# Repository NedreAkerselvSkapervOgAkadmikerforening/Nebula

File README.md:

# Nebula
## Introduksjon
Nebula er foreningen NASAs neste generasjons flydatamaskin til bruk i foreningens modellrakketter.

## 🎯 Mål
1. Nebula skal være rask, kompakt, pålitelig, effektiv og enkel i bruk.
2. Nebula skal være bygd modulært, så nye sensorer og systemer kan innbyttes.
3. Sensorene i Nebula skal være nøyaktige og pålitelige.

## 💽 Oppbygning
Nebula kan overordnet deles i to kategorier:
1. Hovedkort
2. Modulene

### 🏠 Hovedkortet
Hovedkortet er hjernen og master i hele flydatamaskinen. Kortet bruker primært SPI-protokoll til å kommunisere med modulene.

Systemet drives av et enkelt 3.7 V LiPo-batteri, med 3.3 V logikk for alle moduler.

**Sensorer:**
- BMP390 - Trykk- og temperatursensor ([lenke](https://www.3achips.com/p/11139403?utm_source=octopart&utm_medium=cpc&utm_campaign=3achips_launch))
- BNO086 - Akselerometer, gyroskop og magnetometer

**Datalogging:**
- MEM2067-02-180-00-A - Hengslet SD kort modul ([lenke](https://no.mouser.com/ProductDetail/GCT/MEM2067-02-180-00-A?qs=KUoIvG%2F9IlYTw%2Fcc1GlNJA%3D%3D&srsltid=AfmBOooPYGt0VKhHioGUMaVG0J4CpHVvJOKDjSTnPHolRedy0QrVqX5W))

**Telemetri:**
- SX1276 - LoRa transceiver for trådløs kommunikasjon med bakken

**Kommunikasjon:**
- USB-C (alternativt micro USB) – for kommunikasjon med PC og programmering

**Strømforsyning:**
- Voltage divider - For å måle spenningen på batteriet gjennom ADC på mikrokontrolleren
- TPS63020 - 3.3V spenningsregulator (VURDER)
- JST 2-pin - For å koble til batteriet
- Power switch - For å slå av og på hele systemet

**Debugging:**
- Power LED - For å indikere at systemet er på
- Status LED - For å indikere systemstatus (f.eks. feil, normal drift, etc.)

### 📨 SPI
Hovedkortet fungerer som master, modulene som slaves. Hver modul har egen CS‑pin, som kan velges ved å lodde over riktig solder pad (CS1–CS6).

Mikrokontrolleren har totalt fire SPI-busser. 2 reserveres til selve hovedkortet, og 2 til modulene.

### 🖇️ Konnektorer
I alle moduler skal det være en 20 pin konnektor som kobler modulen til hovedkortet. Denne skal ha følgende pinout:
- CS: 6 stk
- MISO: 2 stk
- MOSI: 2 stk
- SCK: 2 stk
- 3vO: 1 stk
- GND: 1 stk
- GPIO: 6 stk

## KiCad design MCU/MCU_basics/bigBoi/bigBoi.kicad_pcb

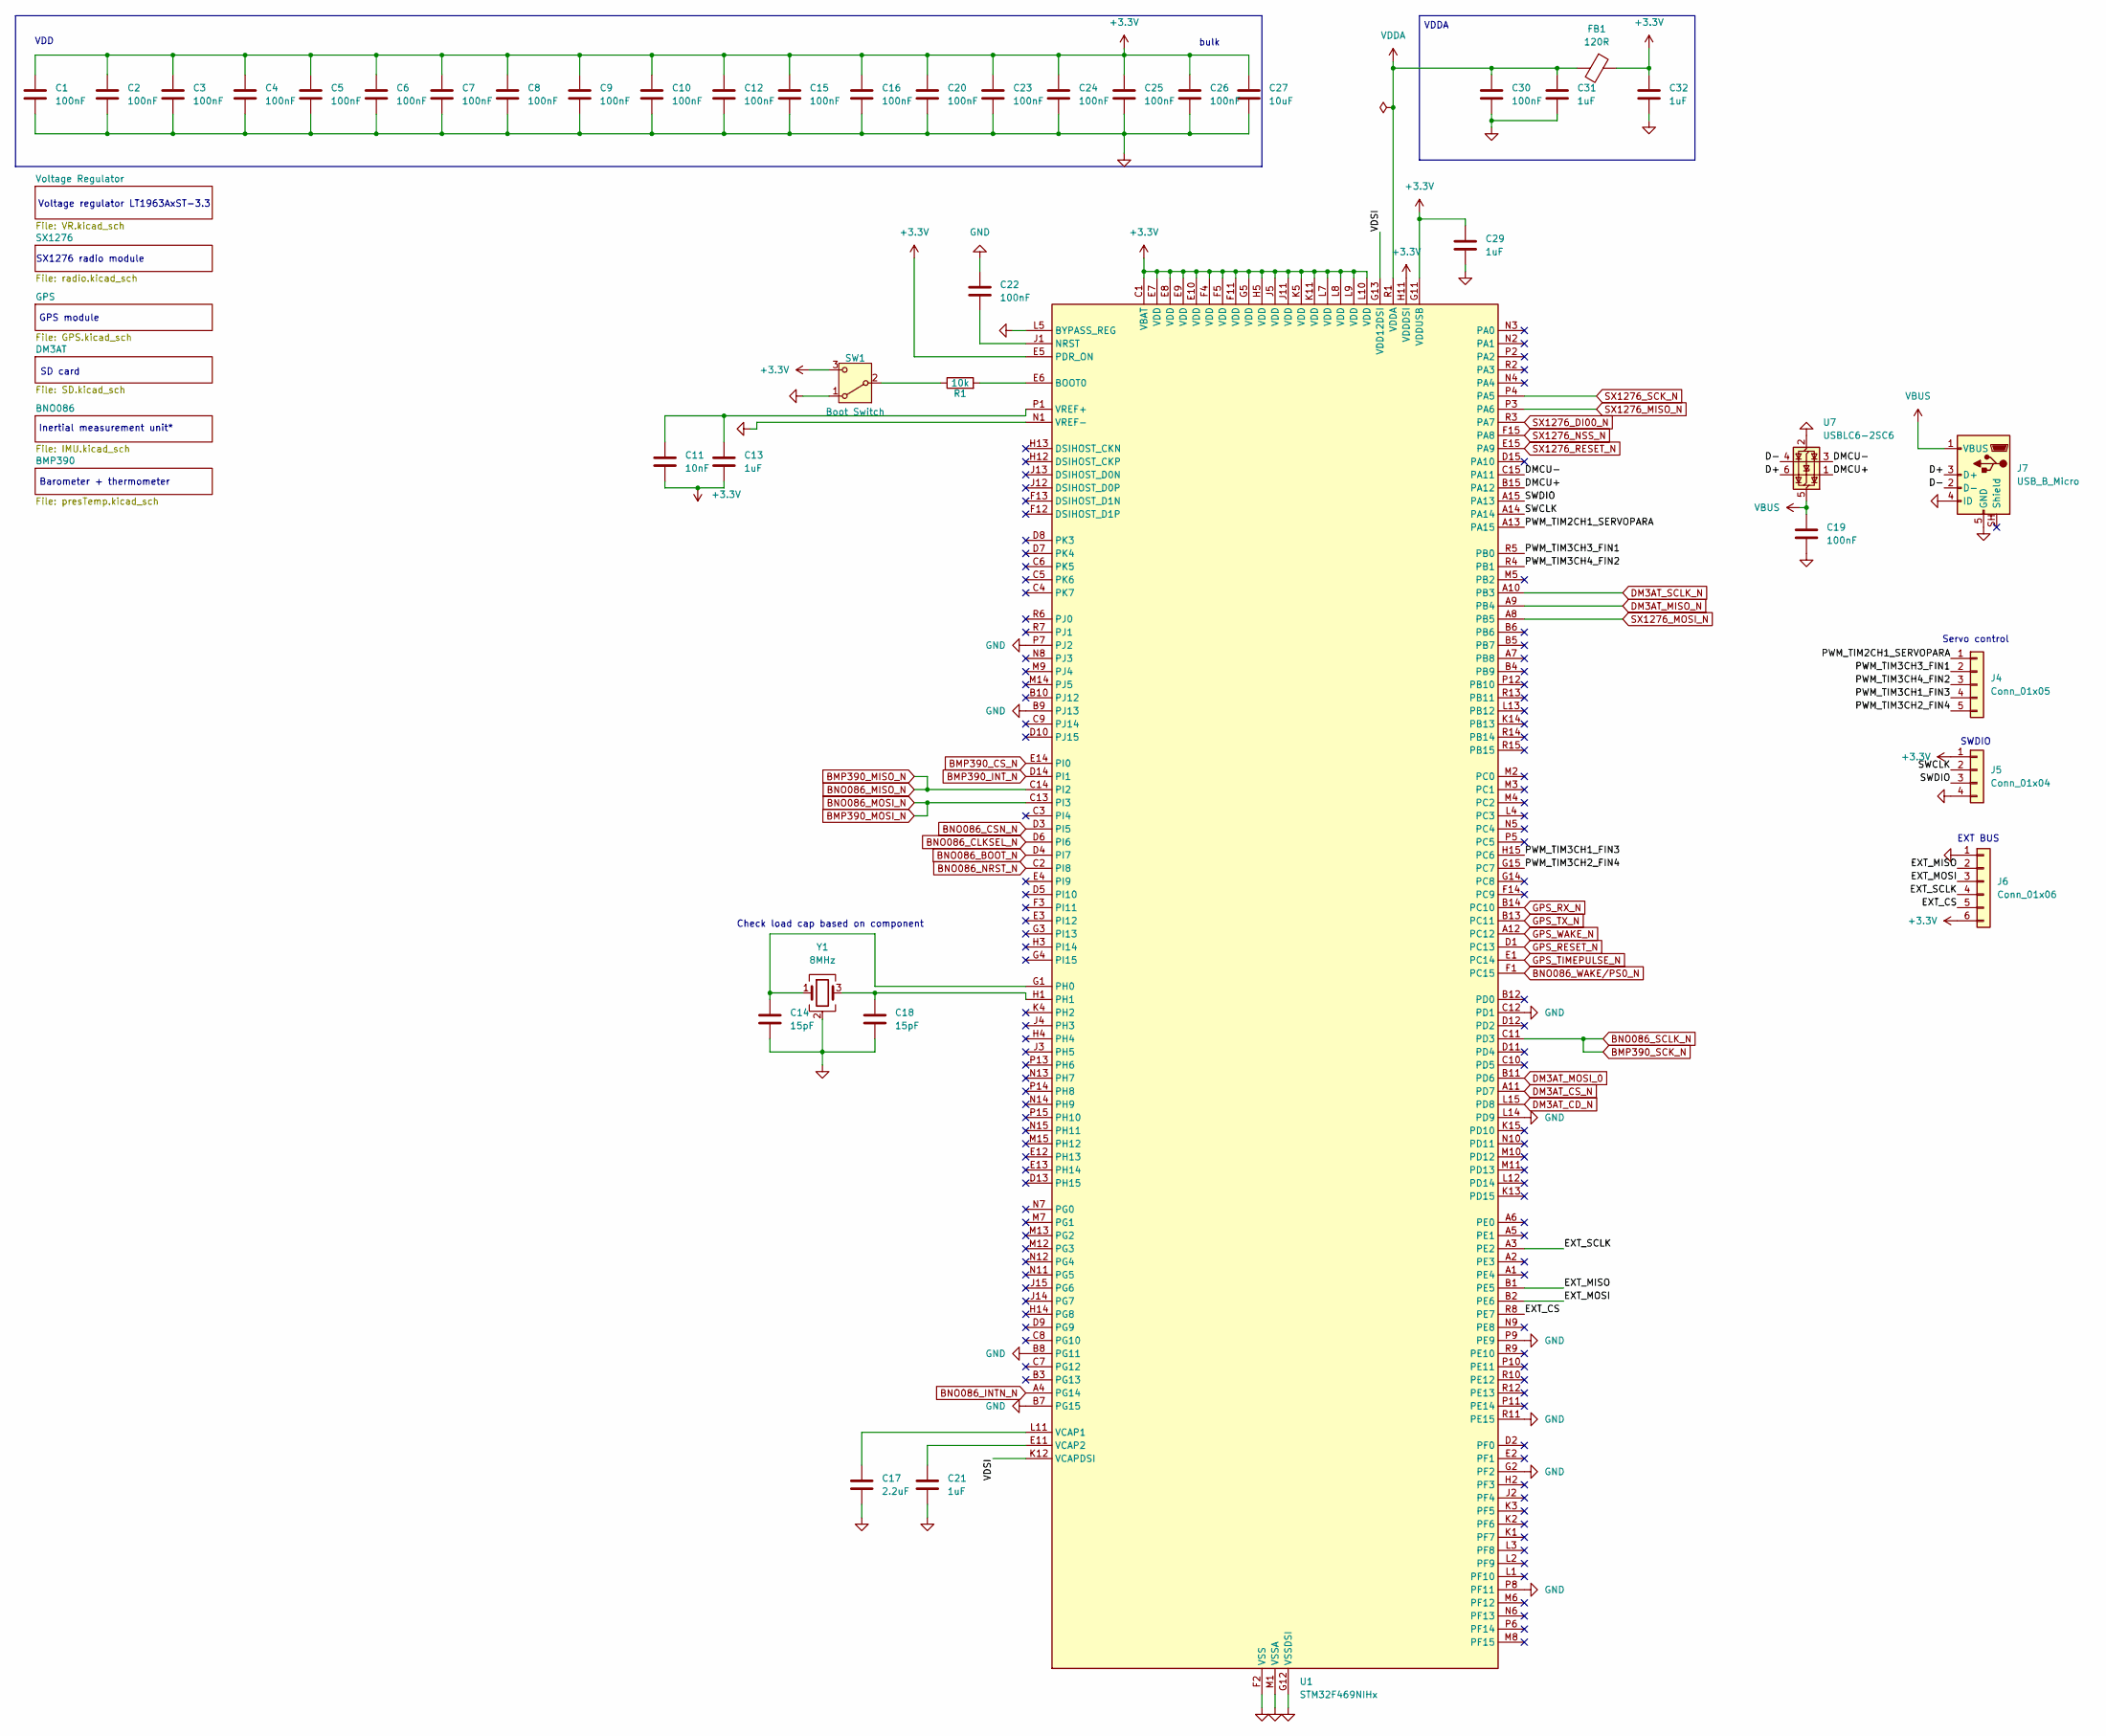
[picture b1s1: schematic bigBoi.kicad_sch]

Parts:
C1, C2, C3, C4, C5, C6, C7, C8, C9, C10, C12, C15, C16, C19, C20, C22, C23, C24, C25, C26, C30: 100nF; C_0402_1005Metric
C11: 10nF; C_0402_1005Metric
C13, C21, C29, C31, C32: 1uF; C_0402_1005Metric
C14, C18: 15pF; C_0402_1005Metric
C17: 2.2uF; C_0603_1608Metric
C27: 10uF; C_0805_2012Metric
FB1: 120R; L_0603_1608Metric
J4: Conn_01x05; PinHeader_1x05_P2.54mm_Vertical
J5: Conn_01x04; PinHeader_1x04_P2.54mm_Vertical
J6: Conn_01x06; PinHeader_1x06_P2.54mm_Vertical
J7: USB_B_Micro; USB_Micro-B_Molex_47346-0001
R1: 10k; R_0402_1005Metric
SW1: Boot Switch; SW_SPDT_PCM12
U1: STM32F469NIHx; TFBGA-216_13x13mm_Layout15x15_P0.8mm
U7: USBLC6-2SC6; SOT-23-6
Y1: 8MHz; Crystal_SMD_3225-4Pin_3.2x2.5mm

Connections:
+3.3V: C1.1, C2.1, C3.1, C4.1, C5.1, C6.1, C7.1, C8.1, C9.1, C10.1, C11.2, C12.1, C13.2, C15.1, C16.1, C20.1, C23.1, C24.1, C25.1, C26.1, C27.1, C29.1, C32.2, FB1.1, J5.1, J6.6, SW1.3 (C), U1.C1 (VBAT), U1.E5 (PDR_ON), U1.E7 (VDD), U1.E8 (VDD), U1.E9 (VDD), U1.E10 (VDD), U1.F4 (VDD), U1.F5 (VDD), U1.F11 (VDD), U1.G5 (VDD), U1.G11 (VDDUSB), U1.H5 (VDD), U1.H11 (VDDDSI), U1.J5 (VDD), U1.J11 (VDD), U1.K5 (VDD), U1.K11 (VDD), U1.L7 (VDD), U1.L8 (VDD), U1.L9 (VDD), U1.L10 (VDD); also elsewhere on the board
/D+: J7.3 (D+), U7.6 (I/O1)
/D-: J7.2 (D-), U7.4 (I/O2)
/DMCU+: U1.B15 (PA12), U7.1 (I/O1)
/DMCU-: U1.C15 (PA11), U7.3 (I/O2)
/EXT_CS: J6.5, U1.R8 (PE7)
/EXT_MISO: J6.2, U1.B1 (PE5)
/EXT_MOSI: J6.3, U1.B2 (PE6)
/EXT_SCLK: J6.4, U1.A3 (PE2)
/PWM_TIM2CH1_SERVOPARA: J4.1, U1.A13 (PA15)
/PWM_TIM3CH1_FIN3: J4.4, U1.H15 (PC6)
/PWM_TIM3CH2_FIN4: J4.5, U1.G15 (PC7)
/PWM_TIM3CH3_FIN1: J4.2, U1.R5 (PB0)
/PWM_TIM3CH4_FIN2: J4.3, U1.R4 (PB1)
/SWCLK: J5.2, U1.A14
/SWDIO: J5.3, U1.A15 (PA13)
/VDSI: U1.G13 (VDD12DSI), U1.K12 (VCAPDSI)
BMP390_CS_N: U1.E14 (PI0); also elsewhere on the board
BMP390_INT_N: U1.D14 (PI1); also elsewhere on the board
BMP390_MISO_N: U1.C14 (PI2); also elsewhere on the board
BMP390_MOSI_N: U1.C13 (PI3); also elsewhere on the board
BMP390_SCK_N: U1.C11 (PD3); also elsewhere on the board
BNO086_BOOT_N: U1.D4 (PI7); also elsewhere on the board
BNO086_CLKSEL_N: U1.D6 (PI6); also elsewhere on the board
BNO086_CSN_N: U1.D3 (PI5); also elsewhere on the board
BNO086_INTN_N: U1.A4 (PG14); also elsewhere on the board
BNO086_NRST_N: U1.C2 (PI8); also elsewhere on the board
BNO086_WAKE/PS0_N: U1.F1 (PC15); also elsewhere on the board
DM3AT_CD_N: U1.L15 (PD8); also elsewhere on the board
DM3AT_CS_N: U1.A11 (PD7); also elsewhere on the board
DM3AT_MISO_N: U1.A9 (PB4); also elsewhere on the board
DM3AT_MOSI_0: U1.B11 (PD6); also elsewhere on the board
DM3AT_SCLK_N: U1.A10 (PB3); also elsewhere on the board
GND: C1.2, C2.2, C3.2, C4.2, C5.2, C6.2, C7.2, C8.2, C9.2, C10.2, C12.2, C14.2, C15.2, C16.2, C17.2, C18.2, C19.2, C20.2, C21.1, C22.1, C23.2, C24.2, C25.2, C26.2, C27.2, C29.2, C30.1, C31.1, C32.1, J5.4, J6.1, J7.4 (ID), J7.5 (GND), SW1.1 (A), U1.B7 (PG15), U1.B8 (PG11), U1.B9 (PJ13), U1.C12 (PD1), U1.F2 (VSS), U1.F6 (VSS), U1.F7 (VSS), U1.F8 (VSS), U1.F9 (VSS), U1.F10 (VSS), U1.G2 (PF2), U1.G6 (VSS), U1.G10 (VSS), U1.G12 (VSSDSI), U1.H6 (VSS), U1.H10 (VSS), U1.J6 (VSS), U1.J10 (VSS), U1.K6 (VSS), U1.K7 (VSS), U1.K8 (VSS), U1.K9 (VSS), U1.K10 (VSS), U1.L5 (BYPASS_REG), U1.L6 (VSS), U1.L14 (PD9), U1.M1 (VSSA), U1.N1 (VREF-), U1.P7 (PJ2), U1.P8 (PF11), U1.P9 (PE9), U1.R11 (PE15), U7.2 (GND), Y1.2 (G), Y1.4 (G); also elsewhere on the board
GPS_RESET_N: U1.D1 (PC13); also elsewhere on the board
GPS_RX_N: U1.B14 (PC10); also elsewhere on the board
GPS_TIMEPULSE_N: U1.E1 (PC14); also elsewhere on the board
GPS_TX_N: U1.B13 (PC11); also elsewhere on the board
GPS_WAKE_N: U1.A12 (PC12); also elsewhere on the board
unnamed: R1.1, SW1.2 (B)
unnamed: R1.2, U1.E6 (BOOT0)
unnamed: C22.2, U1.J1 (NRST)
unnamed: C14.1, U1.G1 (PH0), Y1.1
unnamed: C18.1, U1.H1, Y1.3
unnamed: C17.1, U1.L11 (VCAP1)
unnamed: C21.2, U1.E11 (VCAP2)
unnamed: C11.1, C13.1, U1.P1 (VREF+)
SX1276_DI00_N: U1.R3 (PA7); also elsewhere on the board
SX1276_MISO_N: U1.P3 (PA6); also elsewhere on the board
SX1276_MOSI_N: U1.A8 (PB5); also elsewhere on the board
SX1276_NSS_N: U1.F15 (PA8); also elsewhere on the board
SX1276_RESET_N: U1.E15 (PA9); also elsewhere on the board
SX1276_SCK_N: U1.P4 (PA5); also elsewhere on the board
VBUS: C19.1, J7.1 (VBUS), U7.5 (VBUS); also elsewhere on the board
VDDA: C30.2, C31.2, FB1.2, U1.R1 (VDDA)

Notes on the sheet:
Inertial measurement unit*
bulk
VDD
EXT BUS
GPS module
SD card
VDDA
Voltage regulator LT1963AxST-3.3
Check load cap based on component
SX1276 radio module
Barometer + thermometer
SWDIO
Servo control

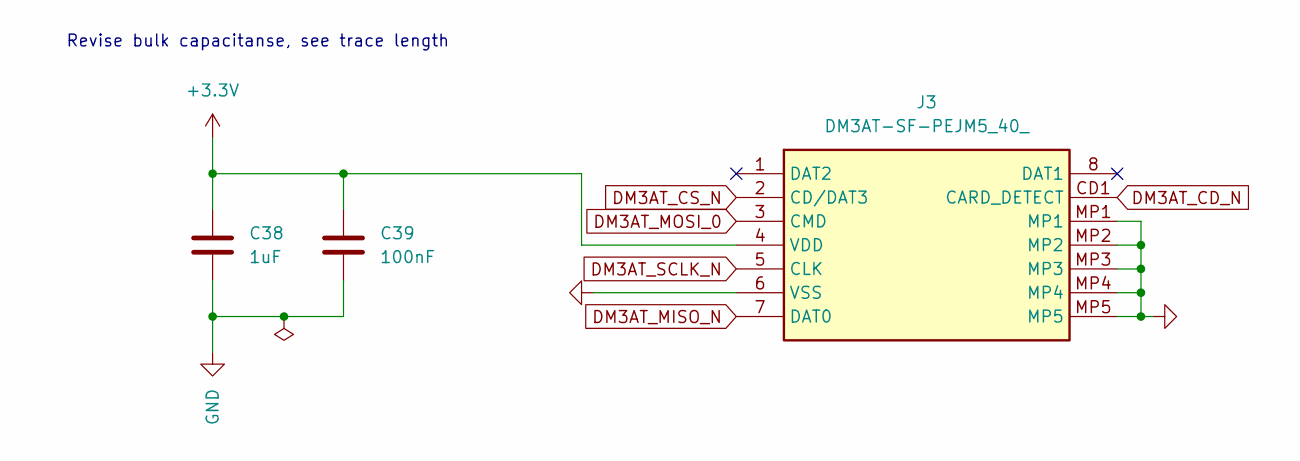
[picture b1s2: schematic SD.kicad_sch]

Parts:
C38: 1uF; C_0402_1005Metric
C39: 100nF; C_0402_1005Metric
J3: DM3AT-SF-PEJM5_40_; DM3ATSFPEJM540; Mouser Part Number 798-DM3AT-SF-PEJM540

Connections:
+3.3V: C38.1, C39.1, J3.4 (VDD); also elsewhere on the board
DM3AT_CD_N: J3.CD1 (CARD_DETECT); also elsewhere on the board
DM3AT_CS_N: J3.2 (CD/DAT3); also elsewhere on the board
DM3AT_MISO_N: J3.7 (DAT0); also elsewhere on the board
DM3AT_MOSI_0: J3.3 (CMD); also elsewhere on the board
DM3AT_SCLK_N: J3.5 (CLK); also elsewhere on the board
GND: C38.2, C39.2, J3.6 (VSS), J3.MP1, J3.MP2, J3.MP3, J3.MP4, J3.MP5; also elsewhere on the board

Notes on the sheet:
Revise bulk capacitanse, see trace length

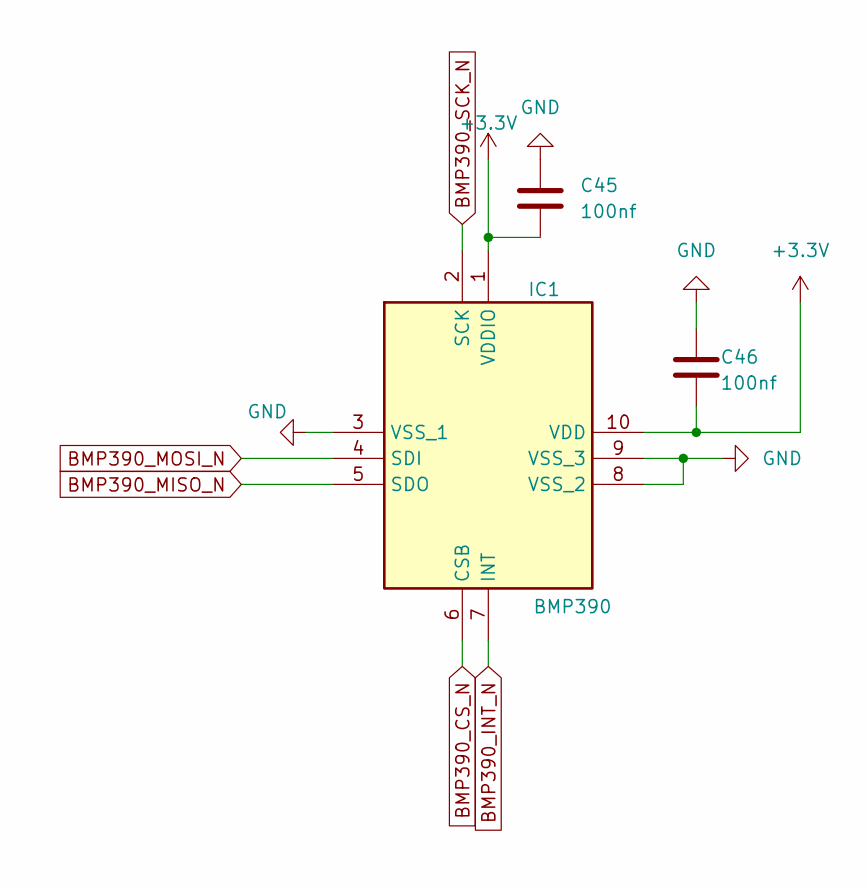
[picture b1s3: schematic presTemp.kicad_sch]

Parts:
C45, C46: 100nf; C_0402_1005Metric
IC1: BMP390; Manufacturer_Part_Number BMP390; Mouser Part Number 262-BMP390

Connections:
+3.3V: C45.2, C46.2, IC1.1 (VDDIO), IC1.10 (VDD); also elsewhere on the board
BMP390_CS_N: IC1.6 (CSB); also elsewhere on the board
BMP390_INT_N: IC1.7 (INT); also elsewhere on the board
BMP390_MISO_N: IC1.5 (SDO); also elsewhere on the board
BMP390_MOSI_N: IC1.4 (SDI); also elsewhere on the board
BMP390_SCK_N: IC1.2 (SCK); also elsewhere on the board
GND: C45.1, C46.1, IC1.3 (VSS_1), IC1.8 (VSS_2), IC1.9 (VSS_3); also elsewhere on the board

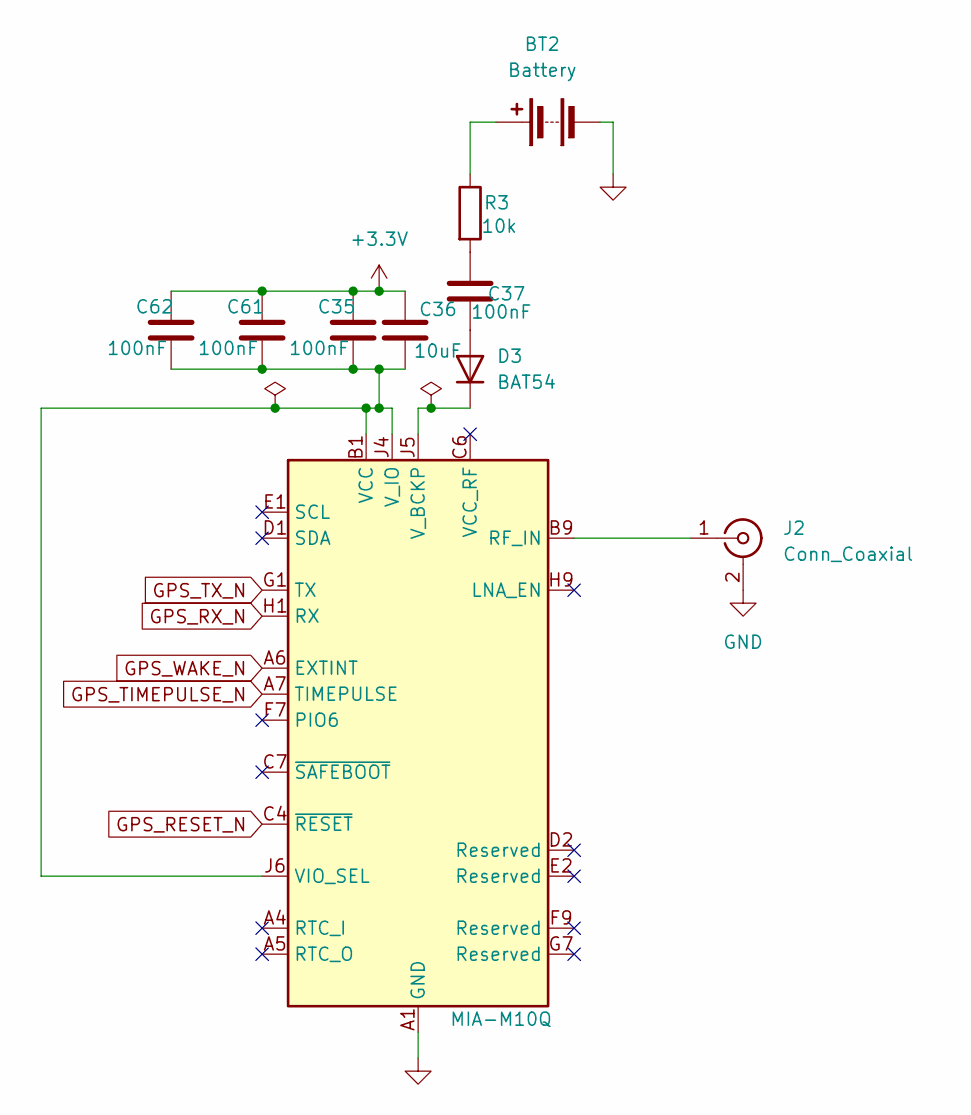
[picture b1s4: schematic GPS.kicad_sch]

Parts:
BT2: Battery; BatteryHolder_LINX_BAT-HLD-012-SMT
C35, C37, C61, C62: 100nF; C_0402_1005Metric
C36: 10uF; C_0603_1608Metric
D3: BAT54; D_0402_1005Metric
J2: Conn_Coaxial; U.FL_Hirose_U.FL-R-SMT-1_Vertical
R3: 10k; R_0402_1005Metric
U5: MIA-M10Q

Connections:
+3.3V: C35.1, C36.1, C61.1, C62.1; also elsewhere on the board
GND: BT2.2 (-), J2.2 (Ext), U5.A1 (GND), U5.A2 (GND), U5.A3 (GND), U5.A8 (GND), U5.A9 (GND), U5.B2 (GND), U5.B8 (GND), U5.C3 (GND), U5.C9 (GND), U5.E3 (GND), U5.E4 (GND), U5.E9 (GND), U5.F1 (GND), U5.F3 (GND), U5.F4 (GND), U5.G3 (GND), U5.G4 (GND), U5.G5 (GND), U5.G6 (GND), U5.H8 (GND), U5.J8 (GND), U5.J9 (GND); also elsewhere on the board
GPS_RESET_N: U5.C4 (~RESET); also elsewhere on the board
GPS_RX_N: U5.H1 (RX); also elsewhere on the board
GPS_TIMEPULSE_N: U5.A7 (TIMEPULSE); also elsewhere on the board
GPS_TX_N: U5.G1 (TX); also elsewhere on the board
GPS_WAKE_N: U5.A6 (EXTINT); also elsewhere on the board
unnamed: BT2.1 (+), R3.1
unnamed: C37.2, R3.2
unnamed: C37.1, D3.2 (A)
unnamed: D3.1 (K), U5.J5 (V_BCKP)
unnamed: J2.1 (In), U5.B9 (RF_IN)
unnamed: C35.2, C36.2, C61.2, C62.2, U5.B1 (VCC), U5.J4 (V_IO), U5.J6 (VIO_SEL)

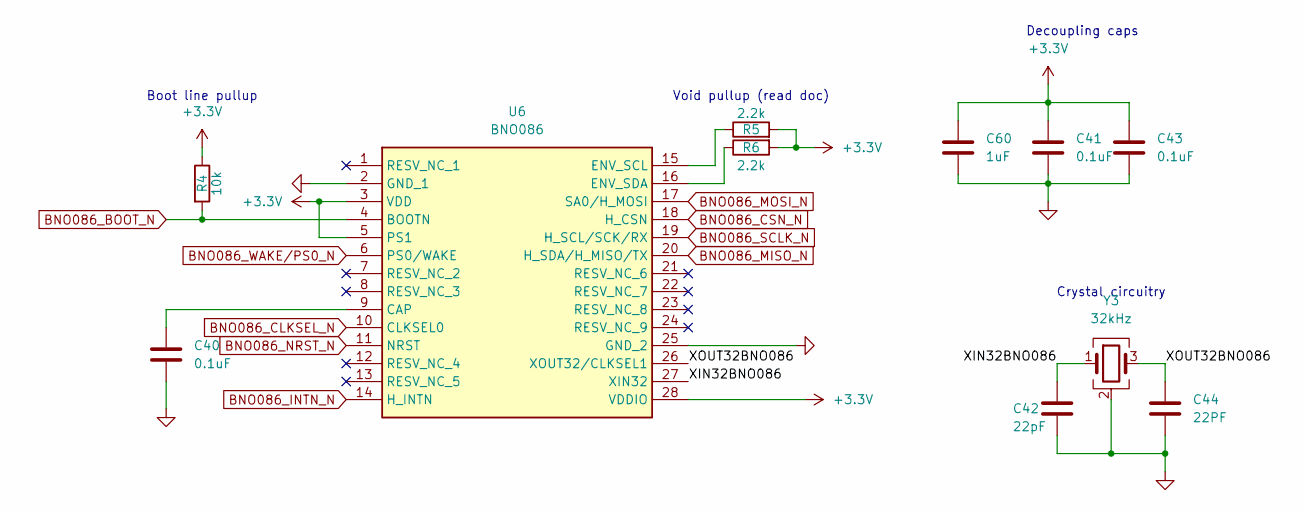
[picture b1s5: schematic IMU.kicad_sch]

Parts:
C40, C41, C43: 0.1uF; C_0402_1005Metric
C42: 22pF; C_0402_1005Metric
C44: 22PF; C_0402_1005Metric
C60: 1uF; C_0402_1005Metric
R4: 10k; R_0402_1005Metric
R5, R6: 2.2k; R_0402_1005Metric
U6: BNO086; Mouser Part Number 526-BNO086
Y3: 32kHz; Crystal_SMD_3225-4Pin_3.2x2.5mm

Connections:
+3.3V: C41.1, C43.1, C60.1, R4.1, R5.2, R6.2, U6.3 (VDD), U6.5 (PS1), U6.28 (VDDIO); also elsewhere on the board
/BNO086/XIN32BNO086: C42.1, U6.27 (XIN32), Y3.1
/BNO086/XOUT32BNO086: C44.1, U6.26 (XOUT32/CLKSEL1), Y3.3
BMP390_MISO_N: U6.20 (H_SDA/H_MISO/TX); also elsewhere on the board
BMP390_MOSI_N: U6.17 (SA0/H_MOSI); also elsewhere on the board
BMP390_SCK_N: U6.19 (H_SCL/SCK/RX); also elsewhere on the board
BNO086_BOOT_N: R4.2, U6.4 (BOOTN); also elsewhere on the board
BNO086_CLKSEL_N: U6.10 (CLKSEL0); also elsewhere on the board
BNO086_CSN_N: U6.18 (H_CSN); also elsewhere on the board
BNO086_INTN_N: U6.14 (H_INTN); also elsewhere on the board
BNO086_NRST_N: U6.11 (NRST); also elsewhere on the board
BNO086_WAKE/PS0_N: U6.6 (PS0/WAKE); also elsewhere on the board
GND: C40.2, C41.2, C42.2, C43.2, C44.2, C60.2, U6.2 (GND_1), U6.25 (GND_2), Y3.2 (G), Y3.4 (G); also elsewhere on the board
unnamed: C40.1, U6.9 (CAP)
unnamed: R5.1, U6.15 (ENV_SCL)
unnamed: R6.1, U6.16 (ENV_SDA)

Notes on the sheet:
Boot line pullup
Decoupling caps
Void pullup (read doc)
Crystal circuitry

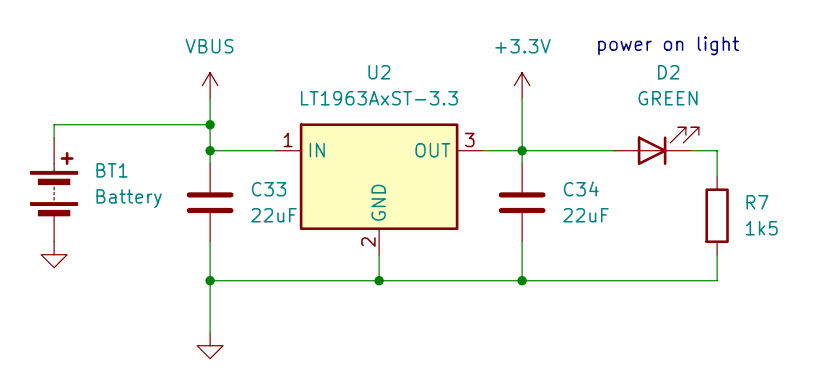
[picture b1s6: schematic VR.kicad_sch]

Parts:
BT1: Battery; JST_PH_S2B-PH-K_1x02_P2.00mm_Horizontal
C33, C34: 22uF; C_0805_2012Metric
D2: GREEN; LED_0603_1608Metric
R7: 1k5; R_0402_1005Metric
U2: LT1963AxST-3.3; SOT-223-3_TabPin2

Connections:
+3.3V: C34.1, D2.2 (A), U2.3 (OUT); also elsewhere on the board
GND: BT1.2 (-), C33.2, C34.2, R7.2, U2.2 (GND); also elsewhere on the board
unnamed: D2.1 (K), R7.1
VBUS: BT1.1 (+), C33.1, U2.1 (IN); also elsewhere on the board

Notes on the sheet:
power on light

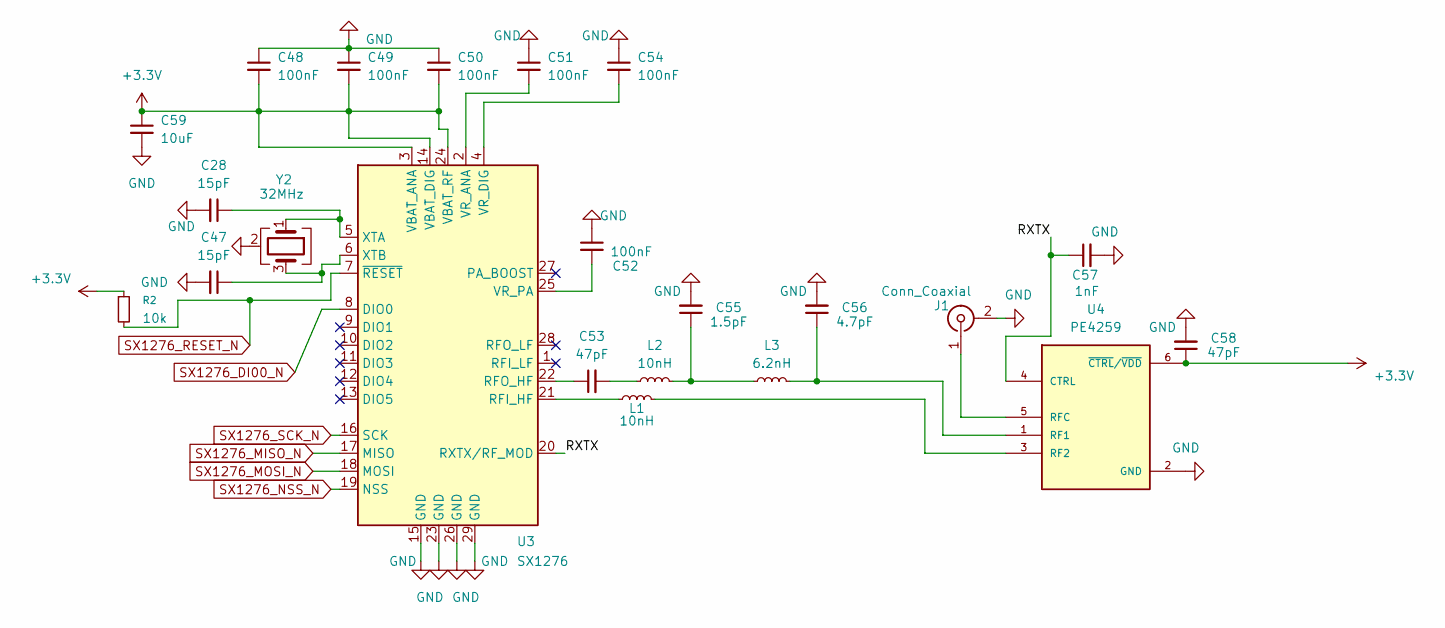
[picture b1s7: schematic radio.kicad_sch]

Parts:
C28, C47: 15pF; C_0402_1005Metric
C48, C49, C50, C51, C52, C54: 100nF; C_0402_1005Metric
C53, C58: 47pF; C_0402_1005Metric
C55: 1.5pF; C_0402_1005Metric
C56: 4.7pF; C_0402_1005Metric
C57: 1nF; C_0402_1005Metric
C59: 10uF; C_0805_2012Metric
J1: Conn_Coaxial; U.FL_Hirose_U.FL-R-SMT-1_Vertical
L1, L2: 10nH; L_0402_1005Metric
L3: 6.2nH; L_0402_1005Metric
R2: 10k; R_0402_1005Metric
U3: SX1276; QFN65P600X600X100-29N
U4: PE4259; SOT65P215X110-6N
Y2: 32MHz; Crystal_SMD_3225-4Pin_3.2x2.5mm

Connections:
+3.3V: C48.2, C49.2, C50.2, C58.1, C59.1, R2.1, U3.3 (VBAT_ANA), U3.14 (VBAT_DIG), U3.24 (VBAT_RF), U4.6 (~CTRL/~VDD); also elsewhere on the board
/SX1276/RXTX: C57.1, U3.20 (RXTX/RF_MOD), U4.4 (CTRL)
GND: C28.2, C47.2, C48.1, C49.1, C50.1, C51.1, C52.1, C54.1, C55.2, C56.2, C57.2, C58.2, C59.2, J1.2 (Ext), U3.15 (GND), U3.23 (GND), U3.26 (GND), U3.29 (GND), U4.2 (GND), Y2.2 (G), Y2.4 (G); also elsewhere on the board
unnamed: C53.2, L2.1
unnamed: C55.1, L2.2, L3.1
unnamed: J1.1 (In), U4.5 (RFC)
unnamed: L1.1, U3.21 (RFI_HF)
unnamed: C53.1, U3.22 (RFO_HF)
unnamed: C51.2, U3.2 (VR_ANA)
unnamed: C54.2, U3.4 (VR_DIG)
unnamed: C52.2, U3.25 (VR_PA)
unnamed: C28.1, U3.5 (XTA), Y2.1
unnamed: C47.1, U3.6 (XTB), Y2.3
unnamed: C56.1, L3.2, U4.1 (RF1)
unnamed: L1.2, U4.3 (RF2)
SX1276_DI00_N: U3.8 (DIO0); also elsewhere on the board
SX1276_MISO_N: U3.17 (MISO); also elsewhere on the board
SX1276_MOSI_N: U3.18 (MOSI); also elsewhere on the board
SX1276_NSS_N: U3.19 (NSS); also elsewhere on the board
SX1276_RESET_N: R2.2, U3.7 (~RESET); also elsewhere on the board
SX1276_SCK_N: U3.16 (SCK); also elsewhere on the board

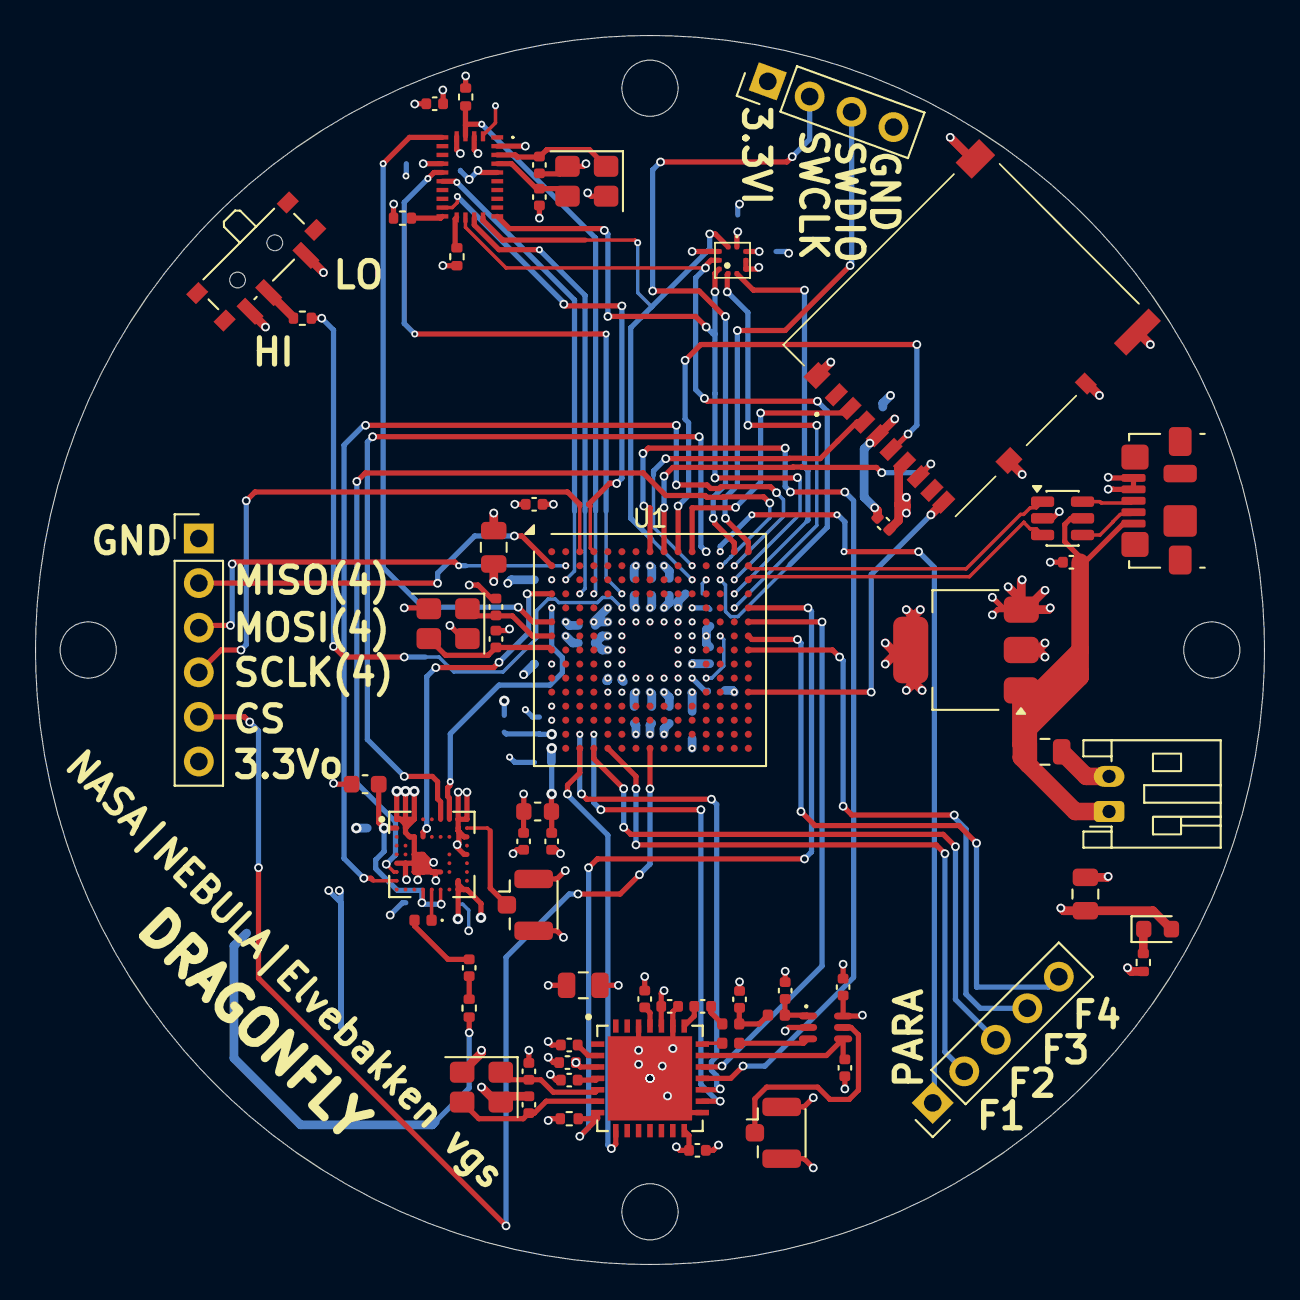
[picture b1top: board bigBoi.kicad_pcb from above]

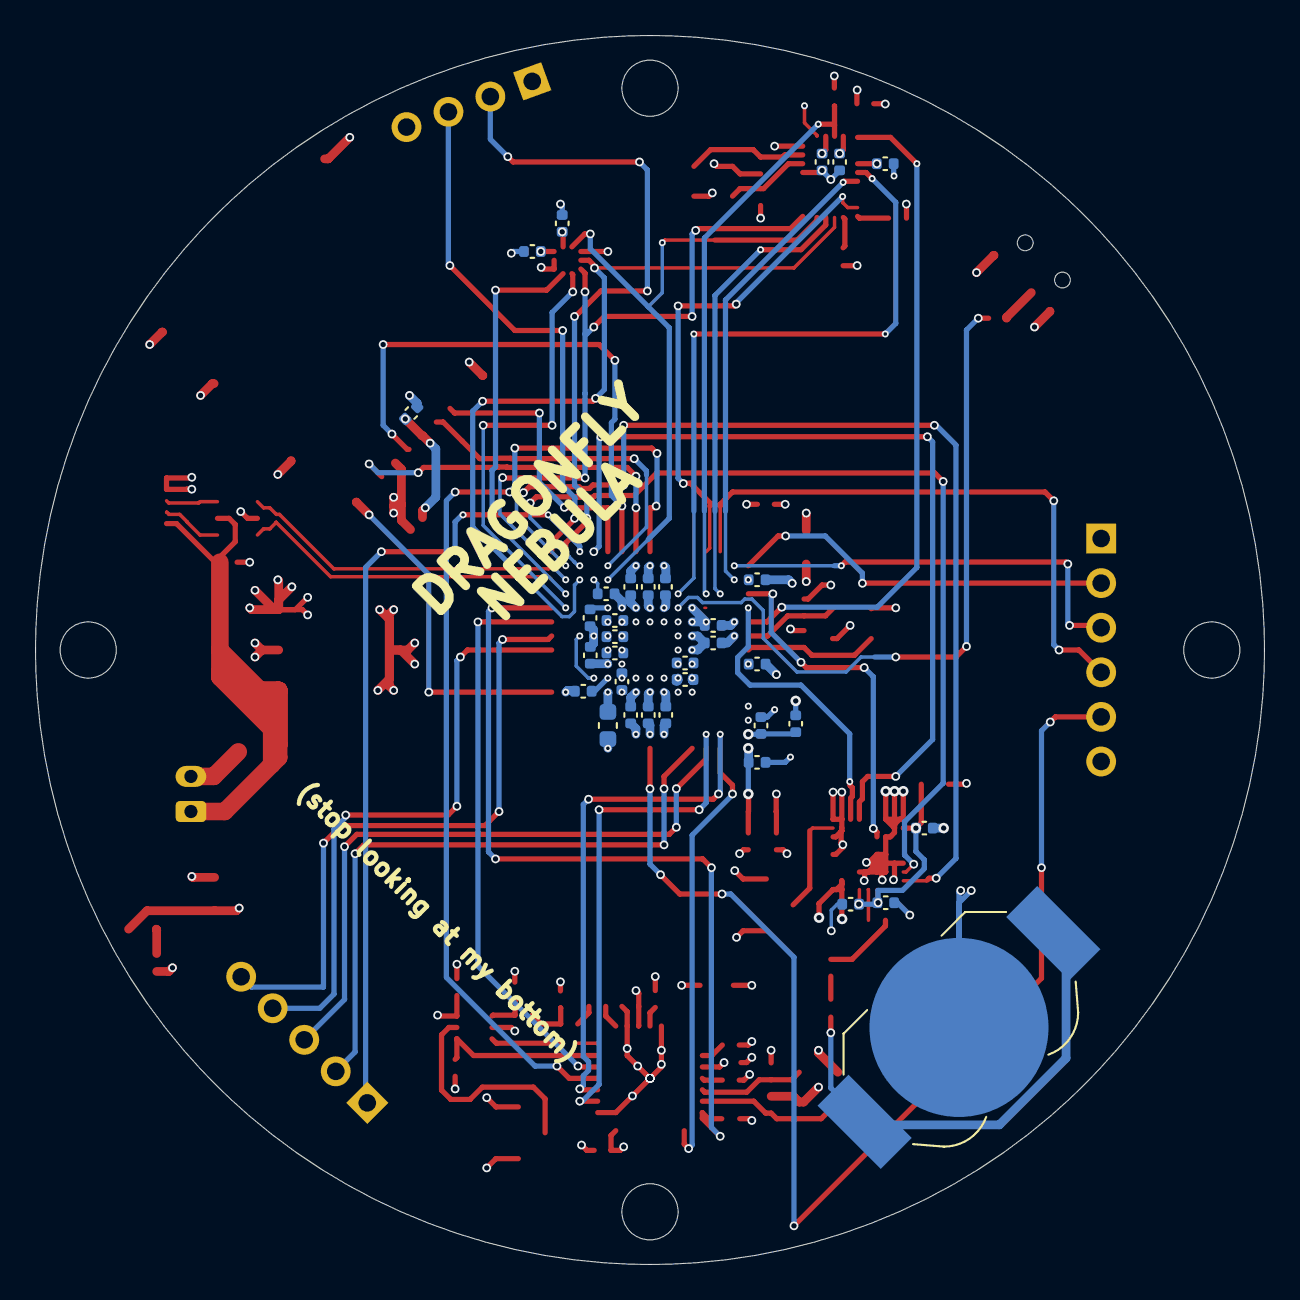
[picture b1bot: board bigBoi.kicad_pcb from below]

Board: 4 copper layers, 70.0 x 70.0 mm, 96 parts (34 on the bottom side), 80 nets.

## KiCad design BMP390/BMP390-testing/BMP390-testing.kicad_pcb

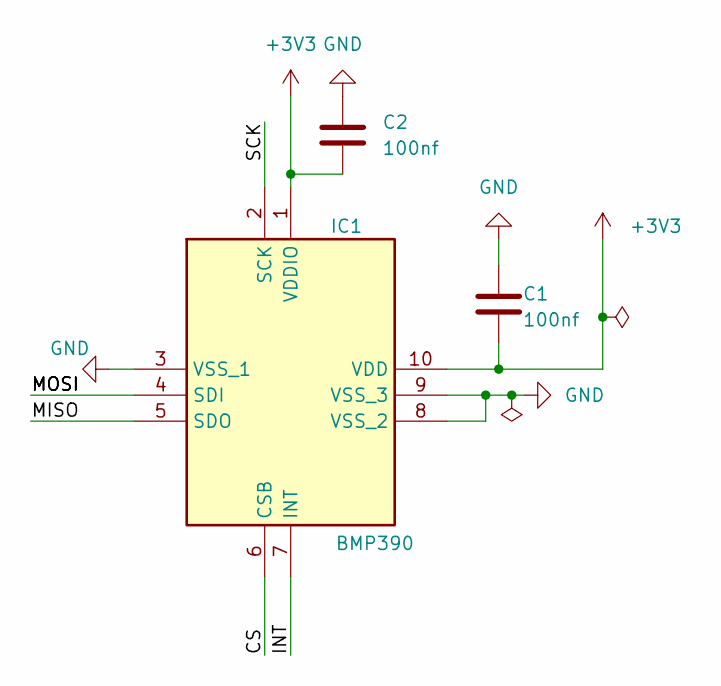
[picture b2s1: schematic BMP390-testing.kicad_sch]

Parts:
C1, C2: 100nf; C_0402_1005Metric
IC1: BMP390; Manufacturer_Part_Number BMP390; Mouser Part Number 262-BMP390

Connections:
+3V3: C1.2, C2.2, IC1.1 (VDDIO), IC1.10 (VDD)
/CS: IC1.6 (CSB)
/INT: IC1.7 (INT)
/MISO: IC1.5 (SDO)
/MOSI: IC1.4 (SDI)
/SCK: IC1.2 (SCK)
GND: C1.1, C2.1, IC1.3 (VSS_1), IC1.8 (VSS_2), IC1.9 (VSS_3)

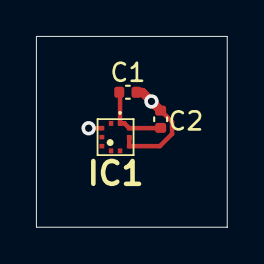
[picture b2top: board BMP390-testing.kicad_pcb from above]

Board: 4 copper layers, 10.6 x 10.6 mm, 3 parts (0 on the bottom side), 2 nets.

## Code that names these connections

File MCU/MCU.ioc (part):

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Mcu.Name=STM32F469NIHx
Mcu.Package=TFBGA216
Mcu.UserName=STM32F469NIHx
PA11.Mode=Device_Only
PA11.Signal=USB_OTG_FS_DM
PA12.Mode=Device_Only
PA12.Signal=USB_OTG_FS_DP
PA13.Mode=Serial_Wire
PA13.Signal=SYS_JTMS-SWDIO
PA14.Mode=Serial_Wire
PA14.Signal=SYS_JTCK-SWCLK
PA15.Signal=S_TIM2_CH1_ETR
PA5.Mode=Full_Duplex_Master
PA5.Signal=SPI1_SCK
PA6.Mode=Full_Duplex_Master
PA6.Signal=SPI1_MISO
PA7.Signal=GPXTI7
PA8.Signal=GPIO_Output
PA9.Signal=GPIO_Output
PB0.Signal=S_TIM3_CH3
PB1.Signal=S_TIM3_CH4
PB3.Mode=Full_Duplex_Master
PB3.Signal=SPI3_SCK
PB4.Mode=Full_Duplex_Master
PB4.Signal=SPI3_MISO
PB5.Mode=Full_Duplex_Master
PB5.Signal=SPI1_MOSI
PC10.Mode=Asynchronous
PC10.Signal=UART4_TX
PC11.Mode=Asynchronous
PC11.Signal=UART4_RX
PC12.Signal=GPIO_Output
PC13.Signal=GPIO_Output
PC15/OSC32_OUT.Signal=GPXTI15
PC6.Signal=S_TIM3_CH1
PC7.Signal=S_TIM3_CH2
PD3.Mode=Full_Duplex_Master
PD3.Signal=SPI2_SCK
PD6.Mode=Full_Duplex_Master
PD6.Signal=SPI3_MOSI
PD7.Signal=GPIO_Output
PD8.Signal=GPIO_Output
PE2.Mode=Full_Duplex_Master
PE2.Signal=SPI4_SCK
PE5.Mode=Full_Duplex_Master
PE5.Signal=SPI4_MISO
PE6.Mode=Full_Duplex_Master
PE6.Signal=SPI4_MOSI
PE7.Signal=GPIO_Output
PG14.Signal=GPXTI14
PH0/OSC_IN.Mode=HSE-External-Oscillator
PH0/OSC_IN.Signal=RCC_OSC_IN
PH1/OSC_OUT.Mode=HSE-External-Oscillator
PH1/OSC_OUT.Signal=RCC_OSC_OUT
PI0.Signal=GPIO_Output
PI1.Signal=GPXTI1
PI2.Mode=Full_Duplex_Master
PI2.Signal=SPI2_MISO
PI3.Mode=Full_Duplex_Master
PI3.Signal=SPI2_MOSI
PI5.Signal=GPIO_Output
PI6.Signal=GPIO_Output
PI7.Signal=GPIO_Output
PI8.Signal=GPIO_Output
RCC.HSE_VALUE=25000000
board=custom

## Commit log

2026-04-02 Add introduction and project goals to README
2026-04-02 Footprint start
2026-04-10 La til lenke for BMP390
2026-04-13 gps schematic
2026-04-13 basic files
2026-04-21 batteri lader scamatik greie
2026-04-27 John Fix Move Lader
2026-04-27 GPS locked in
2026-04-27 Rename SX1276.kicad_prl to SX1276_SCH_Roy/SX1276.kicad_prl
2026-04-27 Rename SX1276-2026-04-27_132220.zip to SX1276_SCH_Roy/Backup/SX1276-2026-04-27_132220.zip
2026-04-27 Rename SX1276-2026-04-27_174133.zip to SX1276_SCH_Roy/Backup/SX1276-2026-04-27_174133.zip
2026-04-27 Rename ~SX1276.kicad_sch.lck to SX1276_SCH_Roy/~SX1276.kicad_sch.lck
2026-04-27 Rename SX1276.kicad_pcb to SX1276_SCH_Roy/SX1276.kicad_pcb
2026-04-27 Rename SX1276.kicad_pro to SX1276_SCH_Roy/SX1276.kicad_pro
2026-04-27 Rename SX1276.kicad_sch to SX1276_SCH_Roy/SX1276.kicad_sch
2026-05-08 software begin
2026-05-11 BNO086 schematic
2026-05-11 Schematic doc
2026-05-12 brUh
2026-05-13 Should be SD
2026-05-13 start MCU power circuit
2026-05-15 Power rails routed
2026-05-15 Rename stuff for Main Chip
2026-05-15 fiksa filsystemer (ish)
2026-05-15 AHHHHHHH
2026-05-15 MCU small update
2026-05-20 more power basics and comm
2026-05-21 BMP390 test
2026-05-21 BMP390 oppdatert til å følge naming convention
2026-05-21 Litt mer naming convention, la den til tilbake johannes 👀👀
2026-05-22 Schematic pins assignment
2026-05-22 schematic connections
2026-05-23 ERC resolving
2026-05-23 ERC hierarchical labeling solved
2026-05-23 fiksa og triksa lit
2026-05-23 most footprints assigned
2026-05-23 update nebula FP
2026-05-23 AHHHH
2026-05-23 La til footprints
2026-05-23 Rydding
2026-05-24 small changes
2026-05-24 Lokale Footprints
2026-05-24 Y2 fixed
2026-05-24 footprints assigned
2026-05-26 Via escape routing
2026-05-26 decoupling cap placement
2026-05-26 MCU pwr+esc
2026-05-26 Store deler av VBUS og USB
2026-05-26 Layout kategorier
2026-05-27 SX1276 layout
2026-05-28 routing complete
